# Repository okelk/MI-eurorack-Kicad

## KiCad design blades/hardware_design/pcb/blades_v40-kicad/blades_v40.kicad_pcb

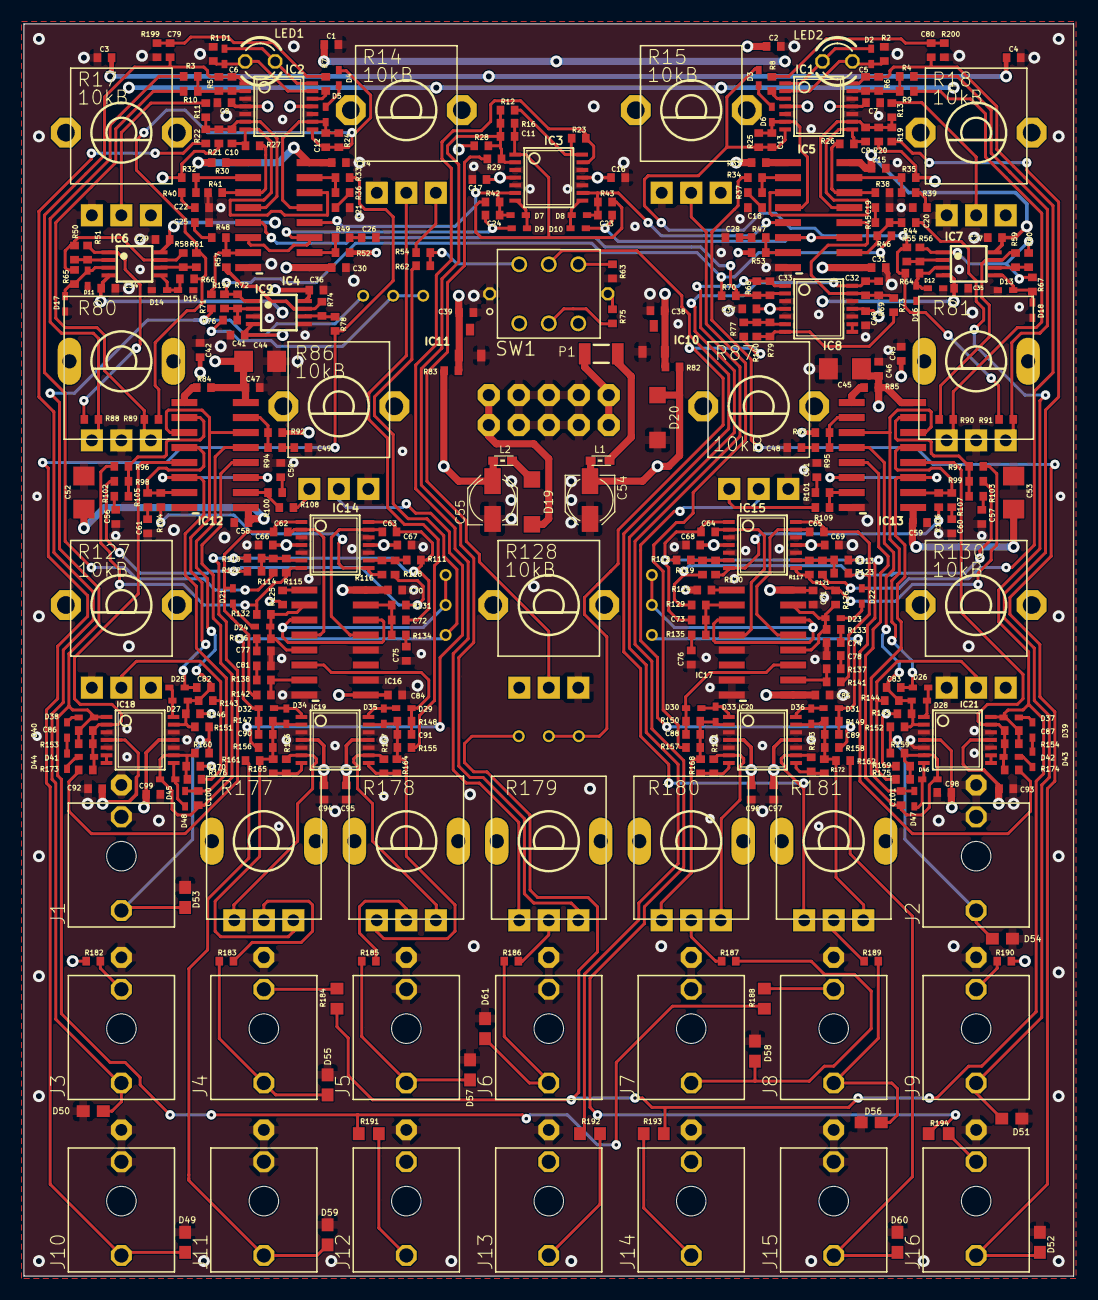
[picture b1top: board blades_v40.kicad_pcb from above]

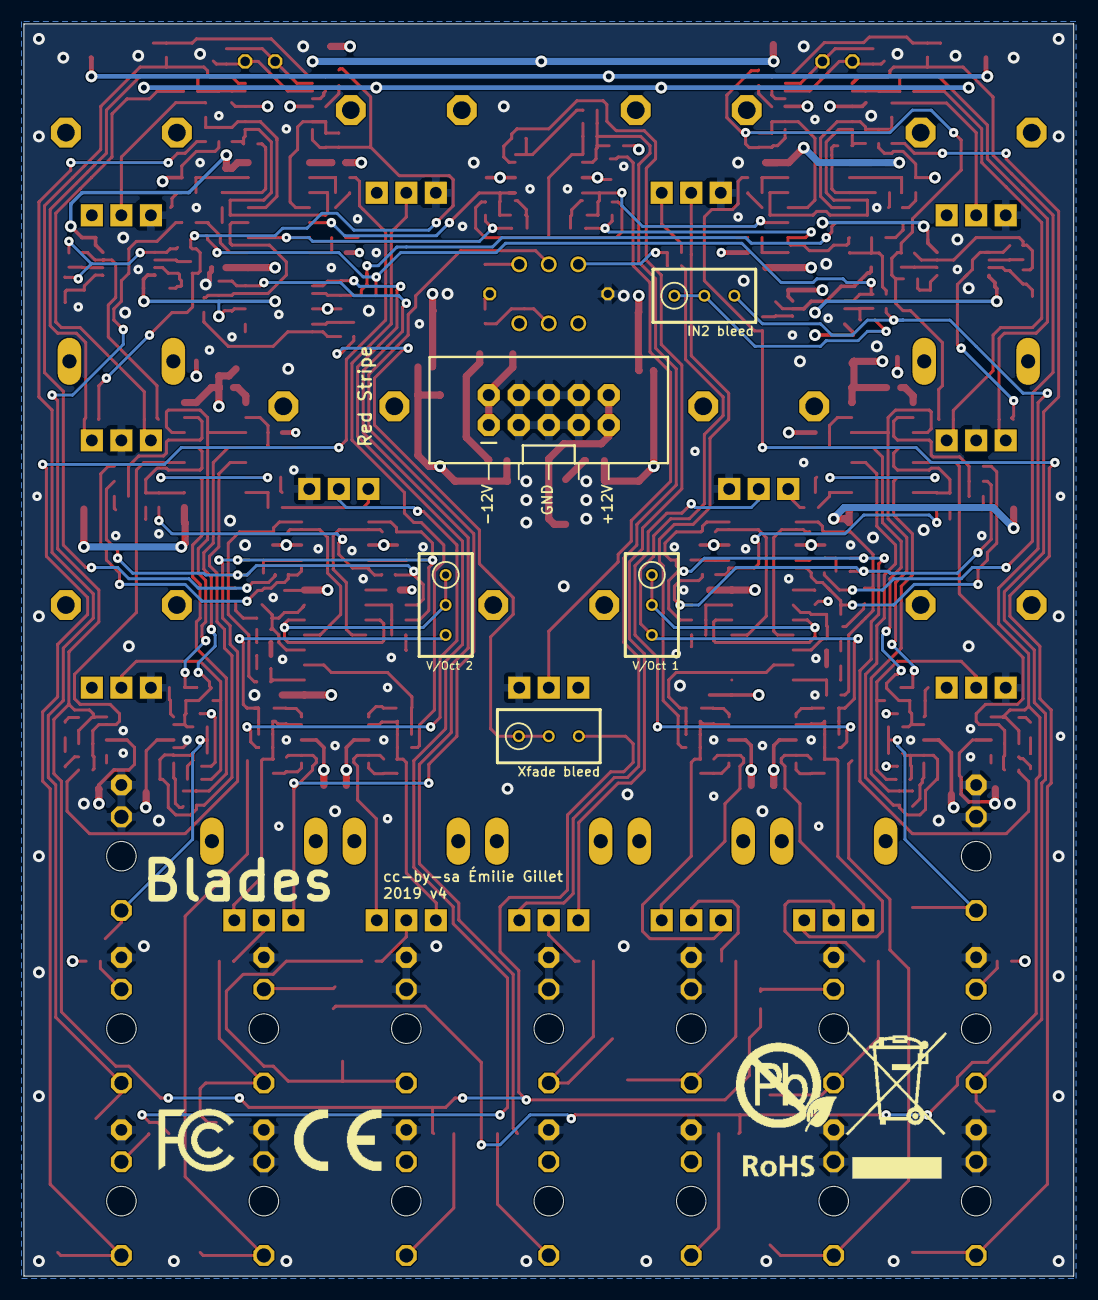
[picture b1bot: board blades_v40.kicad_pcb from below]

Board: 4 copper layers, 88.9 x 106.0 mm, 409 parts (8 on the bottom side), 225 nets.

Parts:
C1, C2, C3, C4, C7, C8, C14, C15, C16, C17, C27, C29, C30, C31, C34, C35, C36, C37, C38, C39, C40, C41, C42, C43, C46, C47, C58, C59, C66, C67, C68, C69, C70, C71, C79, C80, C84, C85, C92, C93, C94, C95, C96, C97, C98, C99: 100n; C0402
C5, C6, C12, C13, C32, C33, C86, C87: 18p; C0402
C9, C10, C11, C23, C24, C62, C63, C64, C65, C82, C83, C88, C89, C90, C91, C100, C101: 220p; C0402
C18, C19, C20, C21, C22, C25, C26, C28, C48, C49, C50, C51, C56, C57, C60, C61, C74, C75, C76, C77, C78, C81: 560p; C0402
C44, C45, C52, C53: 22u; C1206
C54, C55: 22u; PANASONIC_B
C72, C73: DNP; C0402
D1, D2, D7, D8, D9, D10, D11, D12, D13, D14, D15, D16, D17, D18, D25, D26, D27, D28, D29, D30, D31, D32, D33, D34, D35, D36, D45, D46, D47, D48: 1N4148; SOD523
D3, D4, D5, D6, D21, D22, D23, D24, D37, D38, D39, D40, D41, D42, D43, D44: BZT585B5V1T; SOD523
D19, D20: 1N5819HW; SOD123
D49, D50, D51, D52, D53, D54, D55, D56, D57, D58, D59, D60, D61: TVS; 0603
IC1, IC2, IC8, IC14, IC15, IC18, IC21: OPA1679; TSSOP14_065
IC3, IC19, IC20: TL074; TSSOP14_065
IC4, IC5, IC12, IC13, IC16, IC17: V2164SZ; SOIC16N
IC6, IC7, IC9: OPA1678; VSSOP8
IC10, IC11: LM4040B5; DBZ_R-PDSO-G3
J1, J2, J3, J4, J5, J6, J7, J8, J9, J10, J11, J12, J13, J14, J15, J16: PJ301_THONKICONNTME; WQP_PJ_301M_TME
JP1: M05X2SHD; 2X5-SHROUDED
L1, L2: 742792664; 0603
LED1: OSC84L3131A; LED3MM
LED2: OSC54L3131A; LED3MM
P1: PTCSMD; PTC-1206
R1, R2, R30, R31: 6.2k; R0402
R3, R9, R26, R27, R38, R41, R88, R90: 5.1k; R0402
R4, R10, R11, R13, R44, R46, R57, R68, R69, R70, R71, R72, R73, R79, R96, R97, R98, R99, R111, R112, R118, R119, R140, R173, R174, R197: 62.0k; R0402
R5, R6, R52, R92, R93, R108, R109, R145, R146: 200.0k; R0402
R7, R8, R24, R25, R33, R34, R56, R58, R89, R91, R110, R113, R114, R115, R117, R121, R126, R129, R131, R132: 30k; R0402
R12, R16, R23, R42, R43, R53, R143, R144, R151, R152, R159, R160, R161, R162, R175, R176, R183, R186, R189: 100.0k; R0402
R14, R15, R17, R18, R86, R87, R127, R128, R130: 10kB; ALPS_POT_VERTICAL_PS
R19, R22, R32, R35, R50, R51, R55, R59, R60, R61, R63, R64, R65, R66, R67, R155, R157, R185, R187: 100k; R0402
R20, R21, R169, R170: 10M; R0402
R28: 3.9M; R0402
R29: 95.3k; R0402
R36, R37, R39, R40, R45, R47, R48, R49, R75, R94, R95, R100, R101, R102, R103, R105, R107, R133, R134, R135, R136, R137, R138: 510; R0402
R54: 88.7k; R0402
R62, R74, R76, R77, R78, R104, R106, R116, R120, R147, R149, R163, R165, R166, R172: 30.0k; R0402
R80, R81: 10kA; ALPS_POT_NARROW
R82, R83: 1.8k; R0402
R84, R85, R124, R125: 680k; R0402
R122, R123, R199, R200: 300k; R0402
R139, R195, R196, R198: 2k; RTRIM3296W
R141, R142: 15k; R0402
R148, R150, R164, R167, R168, R171: 20k; R0402
R153, R154, R182, R190: 120k; R0402
R156, R158: 44.2k; R0402
R177, R178, R179, R180, R181: 10kB; ALPS_POT_NARROW
R184, R188: DNP; R0603
R191, R192, R193, R194: 1.0k; R0603
SW1: LP4OA1PBCT
U$1: ROHS_BIG
U$2: FCC_MEDIUM
U$3: CE_MEDIUM

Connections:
AREF_+5: C3.1, C4.1, C39.1, IC11.1, R17.P$1, R18.P$1, R28.1, R83.2, R127.P$1, R130.P$1, R182.2, R190.2
AREF_-5: C38.1, C42.1, C43.1, IC10.2, R14.P$1, R15.P$1, R20.1, R21.1, R32.1, R35.1, R52.1, R53.1, R54.1, R82.2, R86.P$3, R87.P$3, R92.1, R93.1, R108.1, R109.1, R128.P$3, R145.1, R146.1, R169.1, R170.1
BP_1: C62.2, D21.A, IC14.1, R98.1, R118.1, R122.2, R131.1, R142.1
BP_2: C65.2, D22.A, IC15.14, R99.1, R119.1, R123.2, R129.1, R141.1
DRIVE_1: C12.2, D4.A, IC2.8, R24.2, R61.1, R66.1, R89.1
DRIVE_2: C13.2, D3.A, IC1.7, R25.2, R55.1, R64.1, R91.1
F1: C24.2, D9.C, IC4.6, IC4.11
F2: C23.2, D10.C, IC5.6, IC5.11
F_CV_1: IC16.3, IC16.14, R196.1, R196.2
F_CV_1_PRE: C90.2, D32.C, R62.1, R147.2, R196.3
F_CV_2: IC17.3, IC17.14, R195.1, R195.2
F_CV_3: R77.1, R139.1, R139.2
GND: C1.1, C2.2, C3.2, C4.2, C7.1, C8.2, C14.2, C15.2, C16.1, C17.2, C18.2, C19.2, C20.2, C21.2, C22.2, C25.2, C26.2, C27.2, C28.2, C29.2, C30.1, C31.1, C34.1, C35.1, C36.2, C37.2, C38.2, C39.2, C40.1, C41.1, C42.2, C43.2, C44.2, C45.2, C46.2, C47.2, C48.2, C49.2, C50.2, C51.2, C52.1, C53.1, C54.+, C55.-, C56.2, C57.2, C58.1, C59.1, C60.2, C61.2, C66.2, C67.1, C68.2, C69.1, C70.2, C71.2, C74.2, C75.2, C76.2, C77.2, C78.2, C81.2, C84.1, C85.1, C92.2, C93.1, C94.2, C95.1, C96.2, C97.1, C98.2, C99.1, D11.C, D12.A, D13.A, D14.C, D15.A, D16.C, D17.A, D18.C, D20.C, D49.1, D50.1, D51.1, D52.1, D53.1, D54.1, D55.1, D56.1, D57.1, D58.1, D59.1, D60.1, D61.1, IC1.5, IC1.10, IC1.12, IC2.3, IC2.5, IC2.10, IC3.3, IC3.5, IC3.10, IC3.12, IC4.8, IC5.8, IC8.3, IC8.5, IC8.10, IC8.12, IC9.3, IC9.5, IC10.1, IC11.2, IC12.8, IC13.8, IC14.3, IC14.5, IC14.10, IC14.12, IC15.3, IC15.5, IC15.10, IC15.12, IC16.8, IC16.10, IC16.12, IC17.5, IC17.7, IC17.8, IC18.3, IC18.5, IC18.10, IC18.12, IC19.3, IC19.5, IC19.10, IC19.12, IC20.3, IC20.5, IC20.10, IC20.12, IC21.3, IC21.5, IC21.10, IC21.12, J1.P1, J1.P2, J2.P1, J2.P2, J3.P1, J4.P1, J5.P1, J5.P2, J6.P1, J6.P2, J7.P1, J7.P2, J8.P1, J9.P1, J10.P1, J10.P2, J11.P1, J11.P2, J12.P1, J13.P1, J14.P1, J15.P1, J15.P2, J16.P1, JP1.3, JP1.4, JP1.5, JP1.6, JP1.7, JP1.8, R1.2, R2.2, R14.P$3, R15.P$3, R17.P$3, R18.P$3, R38.1, R41.1, R63.2, R80.P$2, R81.P$2, R86.P$1, R87.P$1, R127.P$3, R128.P$1, R130.P$3, R199.1, R200.1, SW1.L2
HP_1: IC14.7, R96.1, R115.2, R132.1
HP_2: IC15.8, R97.1, R117.2, R126.1
IN_1: C6.2, C79.1, IC2.1, R5.2, R114.1
IN_1LED1: IC1.3, R8.2
IN_2: C5.2, C80.1, IC1.14, R6.2, R121.1
IN_2_NORMALIZATION: J16.P2, R194.2
LP_1: C63.2, C72.2, IC14.14, R110.2, R111.1, R173.1
LP_2: C64.2, C73.2, IC15.1, R112.1, R113.2, R174.1
MORPH_1A: C82.2, D25.C, IC12.3, IC12.14
MORPH_1A1: C10.2, IC2.7, IC4.14, R27.2
MORPH_1A2: C9.2, IC1.8, IC5.3, R26.2
MORPH_1A3: C83.2, D26.C, IC13.3, IC13.14
MORPH_1B: C100.2, D48.C, IC12.6, IC12.11
MORPH_1B1: C101.2, D47.C, IC13.6, IC13.11
MORPH_CV_1: D53.2, J1.P3, R151.1, R160.1
MORPH_CV_2: D54.2, J2.P3, R152.1, R159.1
MORPH_POT_1: R127.P$2, R143.1, R176.1
MORPH_POT_2: R130.P$2, R144.1, R175.1
unnamed: IC9.6, R74.1, R78.2
unnamed: IC5.10, R44.2, R45.2, R46.2
unnamed: D4.C, D5.C
unnamed: C21.1, R36.1
unnamed: IC8.6, R77.2, R79.1, R140.1
unnamed: IC8.7, R73.1, R79.2, R140.2
unnamed: C77.1, R136.1
unnamed: J12.P3, R191.2
unnamed: IC9.7, R57.1, R74.2
unnamed: IC4.7, R48.2, R57.2, R71.2
unnamed: C32.1, IC5.12, IC8.13, R69.1, R73.2
unnamed: C90.1, D34.A, IC19.2, R147.1, R156.2, R161.2, R165.2, R177.P$1
unnamed: C19.1, R45.1
unnamed: IC9.2, R72.1, R76.2, R197.1
unnamed: C79.2, R7.1, R199.2
unnamed: C25.1, R48.1
unnamed: C33.1, IC4.5, IC8.2, R68.1, R70.2
unnamed: C23.1, D8.A, IC3.9, IC5.5, R43.2
unnamed: IC4.10, R49.2, R52.2
unnamed: C91.1, D35.A, IC19.13, R148.1, R155.2, R164.2, R178.P$3
unnamed: D32.A, D34.C, IC19.1
unnamed: IC4.2, R32.2, R40.2
unnamed: J13.P3, R192.2
unnamed: IC21.8, IC21.9
unnamed: R86.P$2, R156.1
unnamed: D8.C, D10.A, IC3.8
unnamed: R75.1, SW1.P5
unnamed: IC19.9, R167.1, R178.P$1
unnamed: D2.A, IC1.2, LED2.K, R2.1
unnamed: IC19.8, R164.1, R167.2
unnamed: IC2.12, R7.2
unnamed: R178.P$2, R185.2
unnamed: R13.1, R18.P$2
unnamed: C26.1, R49.1
unnamed: C100.1, D45.A, IC12.12, IC18.9, R160.2, R170.2, R176.2
unnamed: IC14.6, R110.1, R114.2, R115.1, R122.1
unnamed: D23.A, IC17.12, IC17.15, R126.2, R133.2
unnamed: R10.1, R80.P$1, R89.2
unnamed: C62.1, IC14.2, IC16.4
unnamed: C75.1, R134.1
unnamed: IC7.2, R55.2, R56.1
unnamed: C72.1, IC16.15, R131.2, R134.2
unnamed: IC6.6, R58.1, R61.2
unnamed: D50.2, J3.P3, R22.1
unnamed: C10.1, IC2.6, IC4.4, R11.2, R21.2, R22.2
unnamed: C63.1, IC14.13, IC16.13
unnamed: C81.1, R138.1
unnamed: R3.1, R80.P$3, R88.2
unnamed: C6.1, IC2.2, R3.2, R5.1, R10.2
unnamed: IC16.7, R138.2, R142.2
unnamed: R11.1, R17.P$2
unnamed: D57.2, J5.P3, R185.1
unnamed: JP1.1, JP1.2, P1.2
unnamed: D19.A, JP1.9, JP1.10
unnamed: D29.A, D35.C, IC19.14
unnamed: C89.2, D31.C, R149.2, R195.3
unnamed: IC18.6, IC18.7
unnamed: IC8.8, IC8.9
unnamed: D12.C, D16.A, IC7.3, R64.2
unnamed: J4.P2, R184.2
unnamed: J8.P2, R188.2
unnamed: C11.1, IC3.2, R12.2, R16.1, R28.2, R29.2, R179.P$1
unnamed: IC4.3, R27.1, R41.2
unnamed: J3.P2, R182.1
unnamed: D61.2, J6.P3, R186.1
unnamed: R14.P$2, R155.1
unnamed: R29.1, R128.P$2
unnamed: IC7.1, R56.2, R60.1, R67.1
unnamed: IC7.6, R59.1, R60.2
unnamed: J9.P2, R190.1
unnamed: C87.1, D42.A, IC13.12, IC21.13, R154.1, R174.2
unnamed: IC12.2, R96.2, R98.2, R102.2
unnamed: IC14.9, R111.2, R116.1, R118.2
unnamed: IC14.8, R104.1, R116.2
unnamed: C24.1, D7.A, IC3.6, IC4.12, R42.2
unnamed: D7.C, D9.A, IC3.7
unnamed: C88.2, D30.C, IC17.11, R150.2
unnamed: IC12.4, IC12.7, R104.2, R105.2
unnamed: C56.1, R102.1
unnamed: C61.1, R105.1
unnamed: D45.C, D48.A, IC18.8
unnamed: IC7.7, R59.2, R90.1
unnamed: IC5.7, R47.2, R53.2
unnamed: C22.1, R40.1
unnamed: C28.1, R47.1
unnamed: IC12.10, R100.2, R108.2
unnamed: IC4.15, R33.2, R36.2
unnamed: IC19.6, R166.1, R177.P$3
unnamed: IC19.7, R165.1, R166.2
unnamed: R177.P$2, R183.2
unnamed: R179.P$2, R186.2
unnamed: D55.2, J4.P3, R183.1
unnamed: D59.2, J11.P3, R161.1
unnamed: IC3.14, R12.1, R23.2
unnamed: D37.C, D39.A
unnamed: IC3.13, R23.1, R179.P$3
unnamed: R75.2, SW1.L1
unnamed: R76.1, R198.1, R198.2
unnamed: D51.2, J9.P3, R19.1
unnamed: C5.1, IC1.13, R4.2, R6.1, R9.2
unnamed: D1.A, IC2.13, LED1.K, R1.1
unnamed: L1.2, P1.1
unnamed: C50.1, R100.1
unnamed: IC12.15, R92.2, R94.2
unnamed: C49.1, R94.1
unnamed: IC4.1, R30.1
unnamed: IC5.1, R31.1
unnamed: C12.1, D5.A, IC2.9, IC4.13, R24.1
unnamed: C82.1, D27.A, IC12.13, IC18.13, R143.2, R146.2, R151.2
unnamed: D25.A, D27.C, IC18.14
unnamed: IC12.1, R84.1
unnamed: IC16.1, R125.1
unnamed: D21.C, D24.C
unnamed: C86.1, D41.A, IC12.5, IC18.2, R153.1, R173.2
unnamed: D38.C, D40.A
unnamed: C80.2, R8.1, R200.2
unnamed: D19.C, L2.2
unnamed: D2.C, IC1.1, LED2.A
unnamed: C9.1, IC1.9, IC5.13, R13.2, R19.2, R20.2
unnamed: IC5.14, R26.1, R38.2
unnamed: IC5.15, R35.2, R39.2
unnamed: C20.1, R39.1
unnamed: C18.1, R37.1
unnamed: IC5.2, R34.2, R37.2
unnamed: R63.1, SW1.P1
unnamed: C13.1, D6.A, IC1.6, IC5.4, R25.1
unnamed: D14.A, D15.C, IC6.5, R66.2
unnamed: D24.A, IC16.2, IC16.5, R132.2, R136.2
unnamed: D1.C, IC2.14, LED1.A
unnamed: C74.1, R133.1
unnamed: IC15.9, R113.1, R117.1, R121.2, R123.1
unnamed: C65.1, IC15.13, IC17.13
unnamed: C76.1, R135.1
unnamed: C73.1, IC17.2, R129.2, R135.2
unnamed: C64.1, IC15.2, IC17.4
unnamed: C78.1, R137.1
unnamed: IC17.10, R137.2, R141.2
unnamed: IC13.15, R97.2, R99.2, R103.2
unnamed: IC15.6, R112.2, R119.2, R120.1
unnamed: IC15.7, R106.1, R120.2
unnamed: IC13.10, IC13.13, R106.2, R107.2
unnamed: C57.1, R103.1
unnamed: C60.1, R107.1
unnamed: IC20.9, R163.1, R181.P$3, SW1.P2
unnamed: IC20.8, R163.2, R172.1
unnamed: R181.P$2, R189.2
unnamed: D56.2, J8.P3, R189.1
unnamed: D60.2, J15.P3, R162.1
unnamed: D30.A, D33.C, IC20.1
unnamed: D13.C, D18.A, IC7.5, R67.2
unnamed: J14.P3, R193.2
unnamed: R87.P$2, R158.1
unnamed: R4.1, R81.P$1, R91.2
unnamed: IC20.6, R171.1, R180.P$1
unnamed: IC20.7, R168.1, R171.2
unnamed: R180.P$2, R187.2
unnamed: D58.2, J7.P3, R187.1
unnamed: R15.P$2, R157.1
unnamed: R54.2, R62.2, SW1.P3
unnamed: C88.1, D33.A, IC20.2, R150.1, R157.2, R168.2, R180.P$3
unnamed: C89.1, D36.A, IC20.13, R149.1, R158.2, R162.2, R172.2, R181.P$1
unnamed: C83.1, D28.A, IC13.4, IC21.2, R144.2, R145.2, R152.2
unnamed: D26.A, D28.C, IC21.1
unnamed: C101.1, D46.A, IC13.5, IC21.6, R159.2, R169.2, R175.2
unnamed: D46.C, D47.A, IC21.7
unnamed: D31.A, D36.C, IC20.14
unnamed: R9.1, R81.P$3, R90.2
unnamed: IC13.7, R101.2, R109.2
unnamed: C51.1, R101.1
unnamed: IC13.2, R93.2, R95.2
unnamed: C48.1, R95.1
unnamed: IC13.1, R85.1
unnamed: IC17.1, R124.1
unnamed: D3.C, D6.C
unnamed: D22.C, D23.C
unnamed: IC6.7, R50.1, R58.2, R65.1
unnamed: IC6.2, R50.2, R51.1
unnamed: IC6.1, R51.2, R88.1
unnamed: D11.A, D17.C, IC6.3, R65.2
unnamed: D40.C, D44.C
unnamed: D41.C, D44.A
unnamed: D42.C, D43.A
unnamed: D39.C, D43.C
OUT: C32.2, IC8.14, R69.2, R192.1
OUT_1: C86.2, D38.A, IC18.1, R71.1, R153.2, R188.1, R191.1, R198.3
OUT_2: C87.2, D37.A, IC21.14, R44.1, R139.3, R154.2, R184.1, R193.1
RAW_IN_1: D49.2, J10.P3, R33.1, R78.1
RAW_IN_2: D52.2, J16.P3, R34.1
RESONANCE_SUM_1: C91.2, D29.C, IC16.6, R148.2
VCC: C2.1, C8.1, C14.1, C15.1, C17.1, C27.1, C29.1, C36.1, C37.1, C44.1, C45.1, C46.1, C47.1, C55.+, C66.1, C68.1, C70.1, C71.1, C92.1, C94.1, C96.1, C98.1, IC1.4, IC2.4, IC3.4, IC4.16, IC5.16, IC6.8, IC7.8, IC8.4, IC9.8, IC12.16, IC13.16, IC14.4, IC15.4, IC16.16, IC17.16, IC18.4, IC19.4, IC20.4, IC21.4, L2.1, R30.2, R31.2, R83.1, R84.2, R85.2, R124.2, R125.2, SW1.P6
VEE: C1.2, C7.2, C16.2, C30.2, C31.2, C34.2, C35.2, C40.2, C41.2, C52.2, C53.2, C54.-, C58.2, C59.2, C67.2, C69.2, C84.2, C85.2, C93.2, C95.2, C97.2, C99.2, D20.A, IC1.11, IC2.11, IC3.11, IC4.9, IC5.9, IC6.4, IC7.4, IC8.11, IC9.4, IC12.9, IC13.9, IC14.11, IC15.11, IC16.9, IC17.9, IC18.11, IC19.11, IC20.11, IC21.11, L1.1, R82.1
ZZZZ: C33.2, IC8.1, R68.2, R194.1
~OUT_1: IC9.1, R46.1, R70.1, R72.2, R197.2
~TOPOLOGY_CV: C11.2, IC3.1, R16.2, R42.1, R43.1

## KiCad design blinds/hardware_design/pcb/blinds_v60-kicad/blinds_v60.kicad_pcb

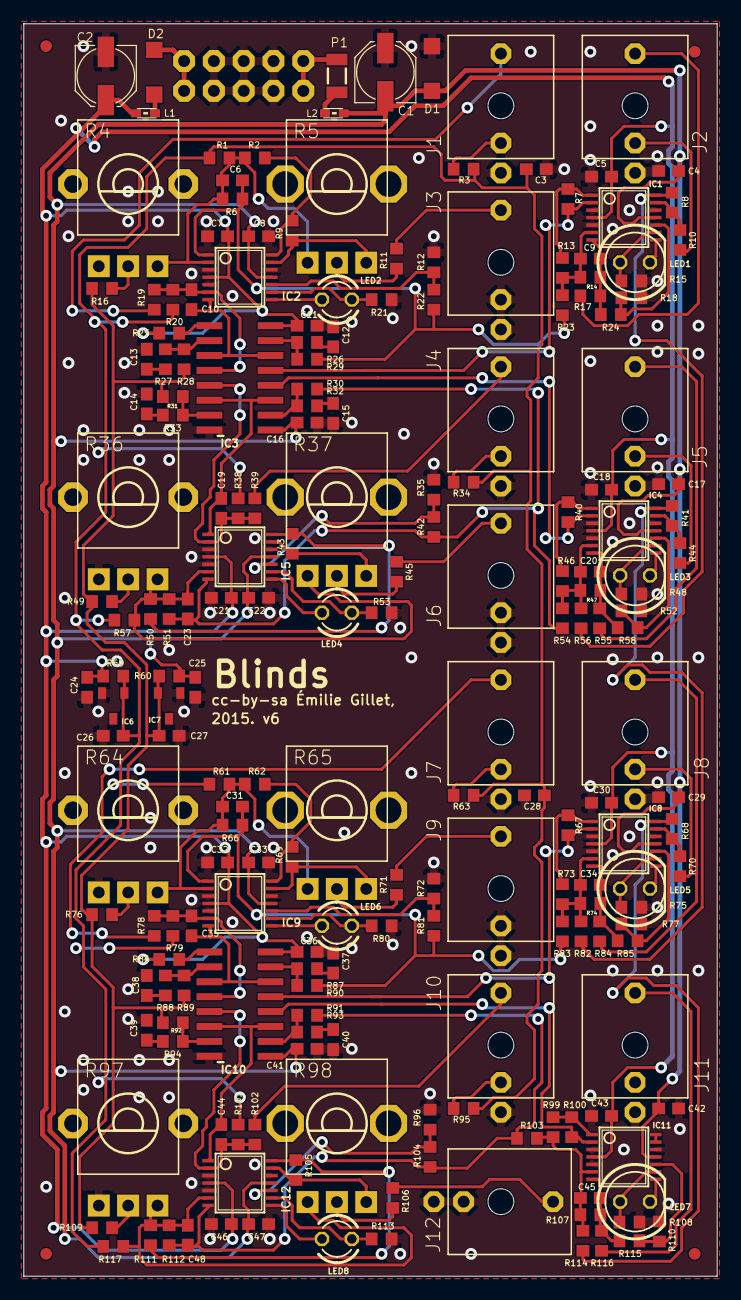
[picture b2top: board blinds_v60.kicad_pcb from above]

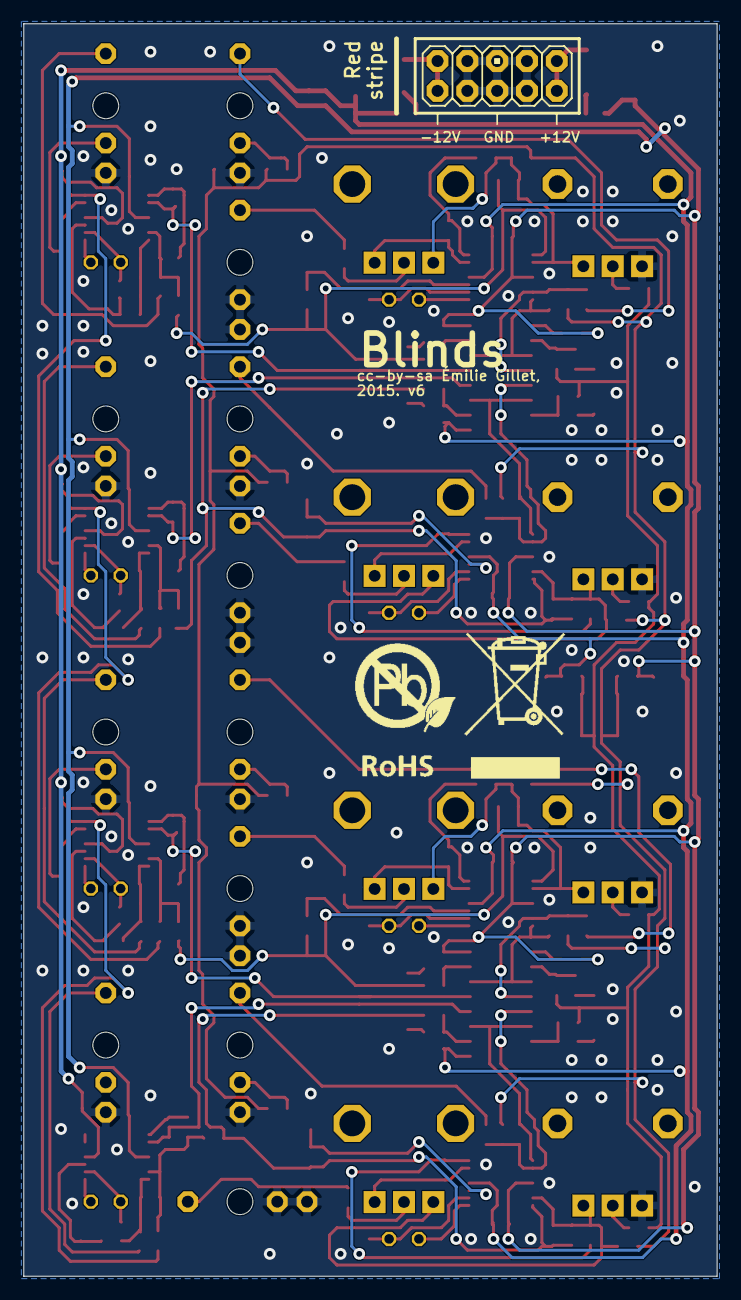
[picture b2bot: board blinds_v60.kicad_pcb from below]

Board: 2 copper layers, 59.1 x 106.7 mm, 208 parts (2 on the bottom side), 125 nets.

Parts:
C1, C2: 22u; PANASONIC_C
C3, C4, C5, C7, C8, C11, C16, C17, C18, C21, C22, C24, C25, C26, C27, C28, C29, C30, C32, C33, C36, C41, C42, C43, C46, C47: 100n; C0603
C6, C9, C10, C19, C20, C23, C31, C34, C35, C44, C45, C48: 47p; C0603
C12, C13, C14, C15, C37, C38, C39, C40: 560p; C0603
D1, D2: 1N5819HW; SOD123
IC1, IC2, IC4, IC5, IC8, IC9, IC11, IC12: OPA4171; TSSOP14
IC3, IC10: V2164SZ; SOIC16N
IC6, IC7: LM4040B10; DBZ_R-PDSO-G3
J1, J2, J3, J4, J5, J6, J7, J8, J9, J10, J11, J12: PJ301_THONKICONN6; WQP_PJ_301M6
JP1, JP2, JP3, JP4: FIDUCIAL1X2; FIDUCIAL-1X2
JP5: M05X2PTH; AVR_ICSP
L1, L2: 0603
LED1, LED3, LED5, LED7: WP7113SRSGW; LED5MM
LED2, LED4, LED6, LED8: WP937EGW; LED3MM
P1: PTCSMD; PTC-1206
R1, R57, R61, R117: 205.0k; R0603
R2, R6, R9, R11, R43, R45, R50, R51, R62, R66, R69, R71, R105, R106, R111, R112: 100k; R0603
R3, R16, R19, R20, R28, R31, R34, R38, R39, R49, R63, R76, R78, R79, R89, R92, R95, R101, R102, R109: 100.0k; R0603
R4, R36, R64, R97: 10kB; ALPS_POT_VERTICAL_PS
R5, R37, R65, R98: 10kB; ALPS_POT_VERTICAL
R7, R8, R13, R40, R41, R46, R67, R68, R73, R99, R100: 4.30k; R0603
R10, R44, R70: 3.90k; R0603
R12, R18, R22, R24, R35, R42, R52, R58, R72, R77, R81, R85, R96, R104, R110, R115: 1.0M; R0603
R14, R47, R56, R74, R82, R107, R114: 66.50k; R0603
R15, R21, R48, R53, R59, R60, R75, R80, R108, R113: 1.2k; R0603
R17, R55, R84, R116: 402; R0603
R23, R29, R30, R54, R83, R90, R91, R103: 33.20k; R0603
R25, R86: DNP; R0603
R26, R27, R32, R33, R87, R88, R93, R94: 510; R0603
U$2: ROHS_BIG

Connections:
1_TO_2: IC1.14, R8.1, R56.2
2_TO_3: IC4.14, R41.1, R82.2
3_TO_4: IC8.14, R68.1, R114.2
AREF_+5: IC11.13, IC11.14
AREF_+10: C3.1, C26.1, C28.1, IC6.1, R1.2, R3.1, R20.2, R34.1, R38.2, R57.2, R59.2, R61.2, R63.1, R79.2, R95.1, R101.2, R117.2
AREF_-10: C27.1, IC7.2, R16.2, R28.2, R31.2, R49.2, R60.2, R76.2, R89.2, R92.2, R109.2
CV_IN_1: J3.P3, R11.2
FOO: IC3.2, R27.2, R28.1
FOO1: IC3.7, R31.1, R33.2
FOO2: IC10.2, R88.2, R89.1
FOO3: IC10.7, R92.1, R94.2
GAIN_1: C6.1, IC2.1, R6.1, R22.2, R23.2, R29.2
GAIN_2: C23.1, IC5.7, R30.2, R42.2, R51.1, R54.2
GAIN_3: C31.1, IC9.1, R66.1, R81.2, R83.2, R90.2
GAIN_4: C48.1, IC12.7, R91.2, R103.2, R104.2, R112.1
GND: C1.+, C2.-, C3.2, C4.1, C5.2, C7.2, C8.1, C11.2, C12.2, C13.2, C14.2, C15.2, C16.1, C17.1, C18.2, C21.2, C22.1, C24.2, C25.2, C26.2, C27.2, C28.2, C29.1, C30.2, C32.2, C33.1, C36.2, C37.2, C38.2, C39.2, C40.2, C41.1, C42.1, C43.2, C46.2, C47.1, D1.C, IC1.3, IC1.5, IC1.12, IC2.3, IC2.5, IC2.12, IC3.8, IC4.3, IC4.5, IC4.12, IC5.3, IC5.5, IC5.12, IC6.2, IC7.1, IC8.3, IC8.5, IC8.12, IC9.3, IC9.5, IC9.12, IC10.8, IC11.3, IC11.5, IC11.12, IC12.3, IC12.5, IC12.12, J1.P1, J2.P1, J3.P1, J3.P2, J4.P1, J5.P1, J6.P1, J6.P2, J7.P1, J8.P1, J9.P1, J9.P2, J10.P1, J11.P1, J12.P1, J12.P2, JP5.3, JP5.4, JP5.5, JP5.6, JP5.7, JP5.8, R4.P$3, R12.2, R15.2, R18.2, R21.2, R35.2, R36.P$3, R48.2, R52.2, R53.2, R64.P$3, R72.2, R75.2, R77.2, R80.2, R96.2, R97.P$3, R108.2, R110.2, R113.2
unnamed: IC3.1, R25.2
unnamed: R4.P$2, R16.1
unnamed: IC1.2, IC3.13, R7.2
unnamed: IC2.8, LED2.K
unnamed: IC2.13, R5.P$1, R9.2
unnamed: J5.P3, R55.1
unnamed: J2.P3, R17.1
unnamed: IC2.14, R2.2, R9.1
unnamed: C6.2, IC2.2, R1.1, R2.1, R4.P$1, R5.P$3, R6.2
unnamed: C9.1, IC1.6, R13.1, R14.2, R23.1
unnamed: D2.A, JP5.1, JP5.2
unnamed: JP5.9, JP5.10, P1.2
unnamed: L2.2, P1.1
unnamed: R5.P$2, R11.1
unnamed: IC2.9, LED2.A, R21.1
unnamed: D2.C, L1.2
unnamed: C15.1, R32.1
unnamed: IC1.8, LED1.K
unnamed: IC1.9, LED1.A, R15.1
unnamed: C13.1, R27.1
unnamed: J1.P3, R19.2
unnamed: IC1.13, R8.2, R10.1
unnamed: J8.P3, R84.1
unnamed: IC3.10, R30.1, R32.2
unnamed: J2.P2, R10.2
unnamed: IC3.12, IC4.2, R40.2
unnamed: C20.1, IC4.6, R46.1, R47.2, R54.1, R56.1
unnamed: J6.P3, R45.2
unnamed: IC5.13, R37.P$1, R43.2
unnamed: IC5.14, R43.1, R50.2
unnamed: C23.2, IC5.6, R36.P$1, R37.P$3, R50.1, R51.2, R57.1
unnamed: R36.P$2, R49.1
unnamed: IC5.8, LED4.K
unnamed: IC5.9, LED4.A, R53.1
unnamed: IC4.8, LED3.K
unnamed: IC4.9, LED3.A, R48.1
unnamed: IC4.13, R41.2, R44.1
unnamed: J5.P2, R44.2
unnamed: IC4.1, R40.1, R46.2
unnamed: R37.P$2, R45.1
unnamed: C14.1, R33.1
unnamed: C19.1, IC3.5, IC5.2, R38.1, R39.1
unnamed: C19.2, IC3.6, IC3.11, IC5.1
unnamed: J4.P3, R39.2
unnamed: C37.1, R87.1
unnamed: IC10.15, R87.2, R90.1
unnamed: C12.1, R26.1
unnamed: IC8.2, IC10.13, R67.2
unnamed: C34.1, IC8.6, R73.1, R74.2, R82.1, R83.1
unnamed: J9.P3, R71.2
unnamed: IC9.13, R65.P$1, R69.2
unnamed: IC9.14, R62.2, R69.1
unnamed: C31.2, IC9.2, R61.1, R62.1, R64.P$1, R65.P$3, R66.2
unnamed: J1.P2, R3.2
unnamed: R64.P$2, R76.1
unnamed: IC9.8, LED6.K
unnamed: IC9.9, LED6.A, R80.1
unnamed: IC8.8, LED5.K
unnamed: IC8.9, LED5.A, R75.1
unnamed: IC8.13, R68.2, R70.1
unnamed: J8.P2, R70.2
unnamed: IC8.1, R67.1, R73.2
unnamed: C38.1, R88.1
unnamed: IC1.1, R7.1, R13.2
unnamed: C10.1, IC2.6, IC3.4, R19.1, R20.1
unnamed: C10.2, IC2.7, IC3.3, IC3.14
unnamed: C35.1, IC9.6, IC10.4, R78.1, R79.1
unnamed: C35.2, IC9.7, IC10.3, IC10.14
unnamed: J10.P3, R102.2
unnamed: R65.P$2, R71.1
unnamed: J11.P3, R116.1
unnamed: C40.1, R93.1
unnamed: IC10.10, R91.1, R93.2
unnamed: IC10.12, IC11.2, R100.2
unnamed: IC3.15, R26.2, R29.1
unnamed: C45.1, IC11.6, R99.1, R103.1, R107.2, R114.1
unnamed: J12.P3, R106.2
unnamed: IC12.13, R98.P$1, R105.2
unnamed: IC12.14, R105.1, R111.2
unnamed: C48.2, IC12.6, R97.P$1, R98.P$3, R111.1, R112.2, R117.1
unnamed: R97.P$2, R109.1
unnamed: IC12.8, LED8.K
unnamed: IC12.9, LED8.A, R113.1
unnamed: IC11.8, LED7.K
unnamed: IC11.9, LED7.A, R108.1
unnamed: IC10.1, R86.2
unnamed: J4.P2, R34.2
unnamed: IC11.1, R99.2, R100.1
unnamed: R98.P$2, R106.1
unnamed: C39.1, R94.1
unnamed: C44.1, IC10.5, IC12.2, R101.1, R102.1
unnamed: C44.2, IC10.6, IC10.11, IC12.1
unnamed: J7.P3, R78.2
unnamed: J7.P2, R63.2
unnamed: J10.P2, R95.2
unnamed: IC1.10, R18.1, R24.1
unnamed: IC4.10, R52.1, R58.1
unnamed: IC8.10, R77.1, R85.1
unnamed: IC2.10, R12.1, R22.1
unnamed: IC11.10, R110.1, R115.1
unnamed: IC12.10, R96.1, R104.1
unnamed: IC9.10, R72.1, R81.1
unnamed: IC5.10, R35.1, R42.1
OUT1: C9.2, IC1.7, R14.1, R17.2, R24.2
OUT2: C20.2, IC4.7, R47.1, R55.2, R58.2
OUT3: C34.2, IC8.7, R74.1, R84.2, R85.2
OUT4: C45.2, IC11.7, R107.1, R115.2, R116.2
VCC: C2.+, C5.1, C7.1, C11.1, C18.1, C21.1, C24.1, C30.1, C32.1, C36.1, C43.1, C46.1, IC1.4, IC2.4, IC3.16, IC4.4, IC5.4, IC8.4, IC9.4, IC10.16, IC11.4, IC12.4, L1.1, R25.1, R59.1, R86.1
VEE: C1.-, C4.2, C8.2, C16.2, C17.2, C22.2, C25.1, C29.2, C33.2, C41.2, C42.2, C47.2, D1.A, IC1.11, IC2.11, IC3.9, IC4.11, IC5.11, IC8.11, IC9.11, IC10.9, IC11.11, IC12.11, L2.1, R60.1

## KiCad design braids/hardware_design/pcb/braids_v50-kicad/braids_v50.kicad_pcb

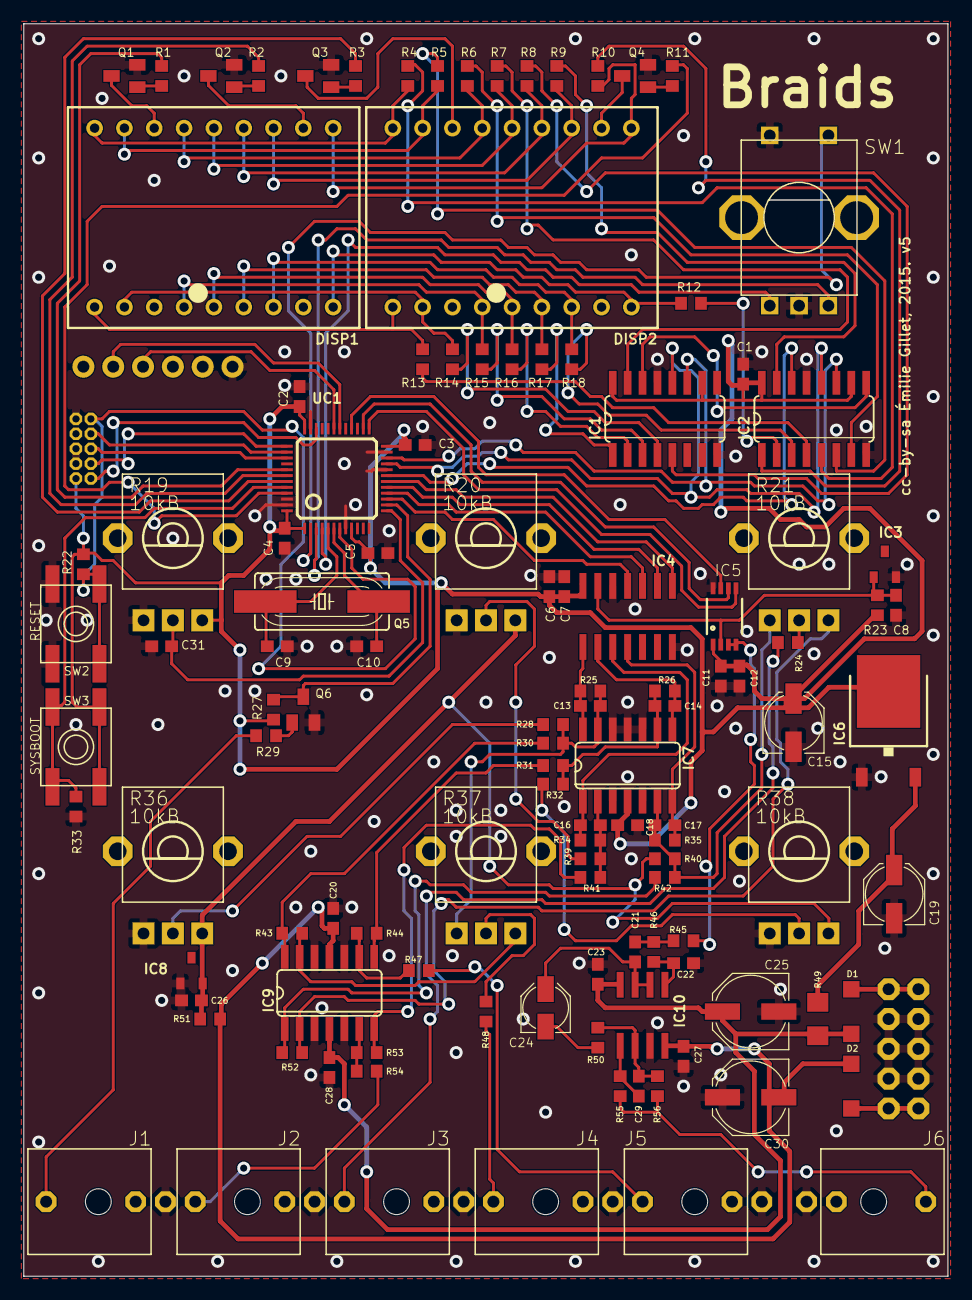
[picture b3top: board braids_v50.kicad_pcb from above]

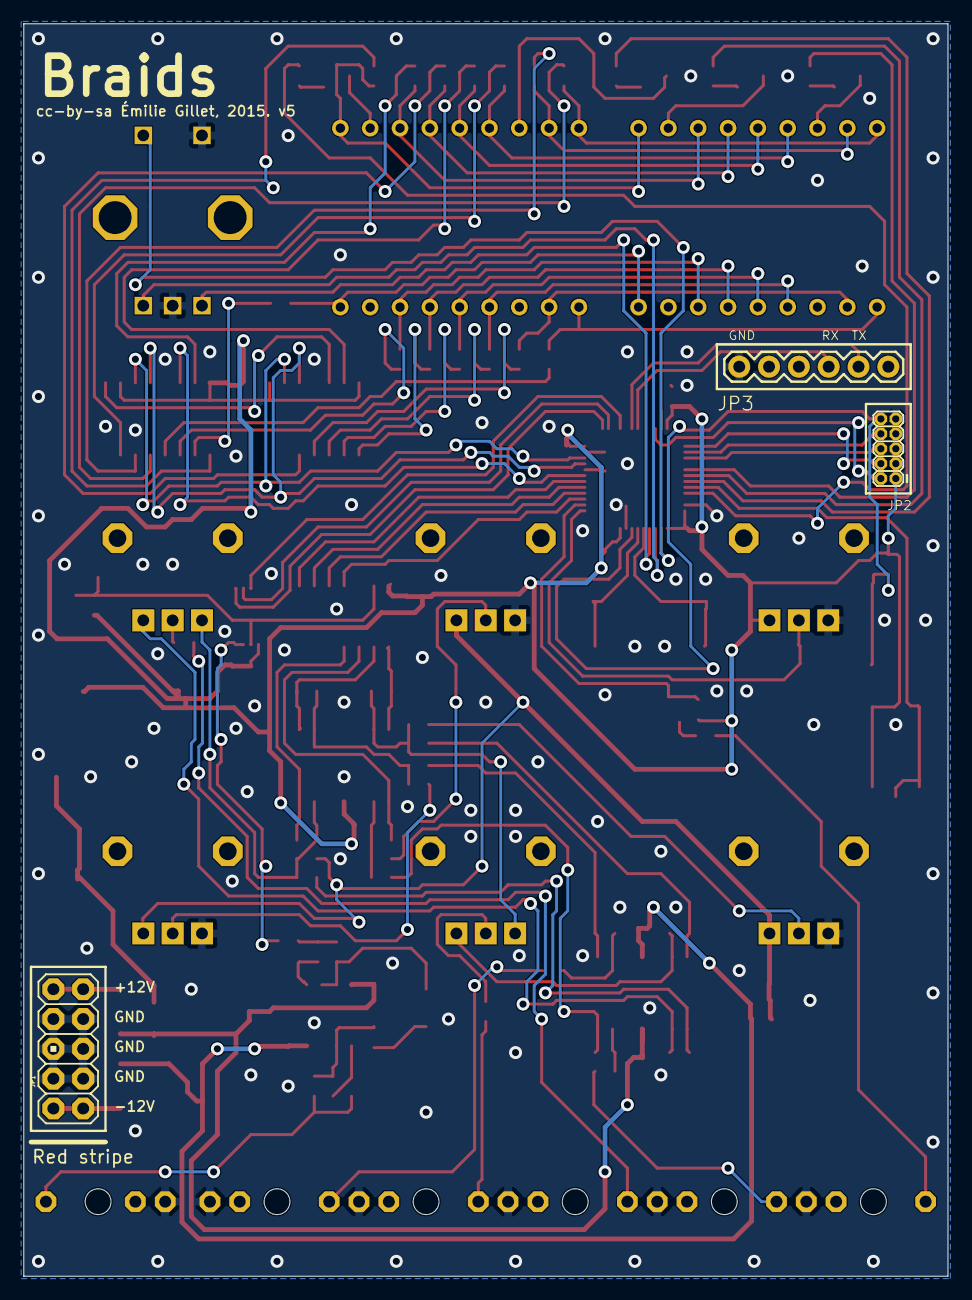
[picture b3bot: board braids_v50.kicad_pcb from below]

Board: 2 copper layers, 78.7 x 106.7 mm, 120 parts (3 on the bottom side), 110 nets.

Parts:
C1, C2, C3, C4, C5, C7, C11, C18, C20, C23, C26, C27, C28, C31: 100n; C0603
C6, C12: 1u; C0603
C8: 470n; C0603
C9, C10: 18p; C0603
C13, C14, C16, C17: 1n; C0603
C15, C19: 22u; PANASONIC_C
C21, C22: 100p; C0603
C24: 10u; PANASONIC_B
C25, C30: 47u; PANASONIC_D
C29: 47p; C0603
D1, D2: 1N5819HW; SOD123
DISP1, DISP2: KINGBRIGHT-PDC54-11; PDC54
IC1, IC2: 74HC595D; SO16
IC3: LM4040B25; DBZ_R-PDSO-G3
IC4: MCP3204; SO14
IC5: DAC8551; MSOP-8
IC6: LM1117-3.3; TO252
IC7: MCP6004; SO14
IC8: LM4040B10; DBZ_R-PDSO-G3
IC9: TL074D; SO14
IC10: TL072; SO08
J1, J2, J3, J4, J5, J6: PJ301_THONKICONN6; WQP_PJ_301M6
JP1: M05X2PTH; AVR_ICSP
JP2: M05X2MINIJTAG; 2X5-1.27
JP3: 1X06
Q1, Q2, Q3, Q4, Q6: MMBT3904; SOT23-BEC
Q5: 8MHz; HC49UP
R1, R2, R3, R11, R23, R55: 1.0k; R0603
R4, R5, R6, R7, R8, R9, R10, R12, R13, R14, R15, R16, R17, R18: 100; R0603
R19, R20, R21, R36, R37, R38: 10kB; ALPS_POT_VERTICAL_PS
R22, R27, R33: 10k; R0603
R24, R29, R47, R48, R54, R56: 100k; R0603
R25, R26: 49.9k; R0603
R28, R32, R40: 200k; R0603
R30, R31, R34, R35, R41, R42, R43, R44, R50, R52, R53: 24.9k; R0603
R39: 120k; R0603
R45, R46: 39k; R0603
R49: 4.7; R1206
R51: 330; R0603
SW1: EC12E_SW; ALPS_EC12E_SW
SW2, SW3: EVQ-Q2
UC1: STM32F103CBT6; LQFP48

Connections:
+3V3: C1.1, C2.1, C3.1, C4.1, C5.1, C6.1, C7.1, C11.1, C12.1, C15.+, C18.1, IC1.10, IC1.16, IC2.10, IC2.16, IC4.14, IC5.1, IC6.3, IC7.4, JP2.1, R19.P$1, R22.2, R23.1, R27.2, SW3.B, SW3.B', UC1.1, UC1.9, UC1.24, UC1.36, UC1.48
ADC_MISO: IC4.10, UC1.16
ADC_MOSI: IC4.9, UC1.17
ADC_SCK: IC4.11, UC1.15
ADC_SS: IC4.8, UC1.18
AREF: C8.1, IC3.1, IC4.13, IC5.2, R23.2
AREF_-10: C26.1, IC8.2, R20.P$1, R36.P$1, R38.P$1, R40.1, R51.2
AUDIO_OUT: IC5.3, IC5.4, R45.2
BOOT_FLASH: R33.2, SW3.A, SW3.A', UC1.44
DAC_MOSI: IC5.7, UC1.28
DAC_SCK: IC5.6, UC1.26
DAC_SS: IC5.5, UC1.25
DISP_CHAR0: R3.1, UC1.43
DISP_CHAR1: R11.1, UC1.45
DISP_CHAR2: R1.1, UC1.41
DISP_CHAR3: R2.1, UC1.42
DISP_EN: IC1.12, IC2.12, UC1.21
DISP_SCK: IC1.11, IC2.11, UC1.22
DISP_SER: IC2.14, UC1.19
ENC_A: SW1.B, UC1.3
ENC_B: SW1.A, UC1.4
ENC_CLICK: SW1.E, UC1.2
FINE_TUNE: C31.1, R19.P$2, UC1.13
FM_CV: C17.2, IC4.4, IC7.7, R35.2
GATE: Q6.C, R27.1, UC1.14
GND: C1.2, C2.2, C3.2, C4.2, C5.2, C6.2, C7.2, C8.2, C9.1, C10.1, C11.2, C12.2, C15.-, C18.2, C19.-, C20.1, C22.2, C23.2, C25.-, C26.2, C27.1, C28.2, C30.+, C31.2, IC1.8, IC1.13, IC2.8, IC2.13, IC3.2, IC4.7, IC4.12, IC5.8, IC6.1, IC7.3, IC7.5, IC7.10, IC7.11, IC7.12, IC8.1, IC9.3, IC9.5, IC9.10, IC9.12, IC10.3, J1.P1, J2.P1, J3.P1, J4.P1, J5.P1, J6.P1, JP1.3, JP1.4, JP1.5, JP1.6, JP1.7, JP1.8, JP2.3, JP2.5, JP2.9, JP3.1, Q1.E, Q2.E, Q3.E, Q4.E, Q6.E, R19.P$3, R20.P$3, R33.1, R36.P$3, R38.P$3, SW1.C, SW1.D, SW2.A, SW2.A', UC1.8, UC1.20, UC1.23, UC1.35, UC1.46, UC1.47
JTCK: JP2.4, UC1.37
JTDI: JP2.8, UC1.38
JTDO: JP2.6, UC1.39
JTMS: JP2.2, UC1.34
unnamed: DISP2.16, Q3.C
unnamed: DISP2.11, Q4.C
unnamed: DISP1.16, Q1.C
unnamed: DISP1.11, Q2.C
unnamed: Q3.B, R3.2
unnamed: Q4.B, R11.2
unnamed: C9.2, Q5.2, UC1.5
unnamed: C10.2, Q5.1, UC1.6
unnamed: Q1.B, R1.2
unnamed: Q2.B, R2.2
unnamed: IC9.7, R41.1, R53.2
unnamed: R20.P$2, R39.1
unnamed: J2.P3, R54.1
unnamed: DISP1.12, DISP2.12, R9.2
unnamed: DISP1.10, DISP2.10, R10.2
unnamed: DISP1.9, DISP2.9, R12.2
unnamed: DISP1.7, DISP2.7, R18.2
unnamed: DISP1.1, DISP2.1, R13.2
unnamed: DISP1.18, DISP2.18, R4.2
unnamed: DISP1.17, DISP2.17, R5.2
unnamed: DISP1.15, DISP2.15, R6.2
unnamed: DISP1.14, DISP2.14, R7.2
unnamed: DISP1.6, DISP2.6, R17.2
unnamed: DISP1.5, DISP2.5, R16.2
unnamed: DISP1.4, DISP2.4, R15.2
unnamed: DISP1.2, DISP2.2, R14.2
unnamed: DISP1.13, DISP2.13, R8.2
unnamed: C16.1, IC7.2, R34.1, R39.2, R41.2
unnamed: IC2.7, R6.1
unnamed: IC1.14, IC2.9
unnamed: IC2.15, R9.1
unnamed: IC2.1, R10.1
unnamed: IC2.2, R12.1
unnamed: IC2.3, R18.1
unnamed: IC2.4, R13.1
unnamed: IC2.5, R4.1
unnamed: IC2.6, R5.1
unnamed: IC1.15, R7.1
unnamed: IC1.1, R17.1
unnamed: IC1.2, R16.1
unnamed: IC1.3, R15.1
unnamed: IC1.4, R14.1
unnamed: IC1.5, R8.1
unnamed: IC9.6, R53.1, R54.2
unnamed: J3.P3, R24.1
unnamed: J4.P3, R48.1
unnamed: R21.P$2, R24.2
unnamed: C19.+, IC6.2, R49.1
unnamed: IC9.13, R37.P$1, R43.1
unnamed: IC9.14, R30.1, R43.2
unnamed: IC9.2, R21.P$1, R52.1
unnamed: IC9.1, R42.1, R52.2
unnamed: C17.1, IC7.6, R21.P$3, R35.1, R40.2, R42.2
unnamed: D1.A, JP1.1, JP1.2
unnamed: J1.P3, R29.1
unnamed: IC9.8, R31.1, R44.2
unnamed: C13.1, IC7.13, R25.1, R28.2, R30.2, R37.P$3
unnamed: J5.P3, R47.1
unnamed: R28.1, R36.P$2
unnamed: R37.P$2, R48.2
unnamed: IC9.9, R44.1, R47.2
unnamed: D2.C, JP1.9, JP1.10
unnamed: R32.1, R38.P$2
unnamed: Q6.B, R29.2
unnamed: C21.2, C24.+, IC10.6, IC10.7
unnamed: C24.-, R50.2
unnamed: C22.1, IC10.5, R46.1
unnamed: C14.1, IC7.9, R26.1, R31.2, R32.2
unnamed: C21.1, R45.1, R46.2
unnamed: J6.P3, R55.1, R56.1
unnamed: C29.2, IC10.1, R55.2
unnamed: C29.1, IC10.2, R50.1, R56.2
PARAM1_CV: C13.2, IC4.1, IC7.14, R25.2
PARAM2_CV: C14.2, IC4.2, IC7.8, R26.2
PITCH_CV: C16.2, IC4.3, IC7.1, R34.2
RESET: JP2.10, R22.1, SW2.B, SW2.B', UC1.7
RX: JP3.4, UC1.31
TX: JP3.5, UC1.30
VCC: C23.1, C25.+, C28.1, D1.C, IC9.4, IC10.8, R49.2
VEE: C20.2, C27.2, C30.-, D2.A, IC9.11, IC10.4, R51.1

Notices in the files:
blades/hardware_design/pcb/blades_v40-kicad/blades_v40.kicad_pcb:
cc-by-sa É. Gillet
cc-by-sa Émilie Gillet
braids/hardware_design/pcb/braids_v50-kicad/braids_v50.kicad_pcb:
cc-by-sa Émilie Gillet, 2015. v5
clouds/hardware_design/pcb/clouds_v30-kicad/clouds_v30.kicad_pcb:
cc-by-sa Émilie Gillet, 2015. v3
cvpal/cvpal/hardware_design/pcb/cvpal_v01-kicad/cvpal_v01.kicad_pcb:
cc-by-sa 2013
ears/hardware_design/pcb/ears_v40-kicads/ears_v40.kicad_pcb:
cc-by-sa Émilie Gillet, 2016.
cc-by-sa Tom Whitwell, 2014.
